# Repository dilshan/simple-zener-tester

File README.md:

# Experimental Zener Diode Tester

Automatic Zener diode tester is capable of identifying Zener diodes up to 27.5V. Apart from that, it can be used to recognize leads of the diodes/Zeners and detect damaged diodes.

This tester is designed using well-known ICs such as MC34063 and PIC16F88.

This unit provides approximately 5% to 15% accurate readings. Based on our observations, the accuracy of this unit can increase by using resistors with 1% tolerance, stable booster circuit, accurate sampling method(s), and with a more optimized PCB layout.

### More prototypes

The following photographs illustrate the prototype version build by [Boris Peshev](https://github.com/BaiBorko).

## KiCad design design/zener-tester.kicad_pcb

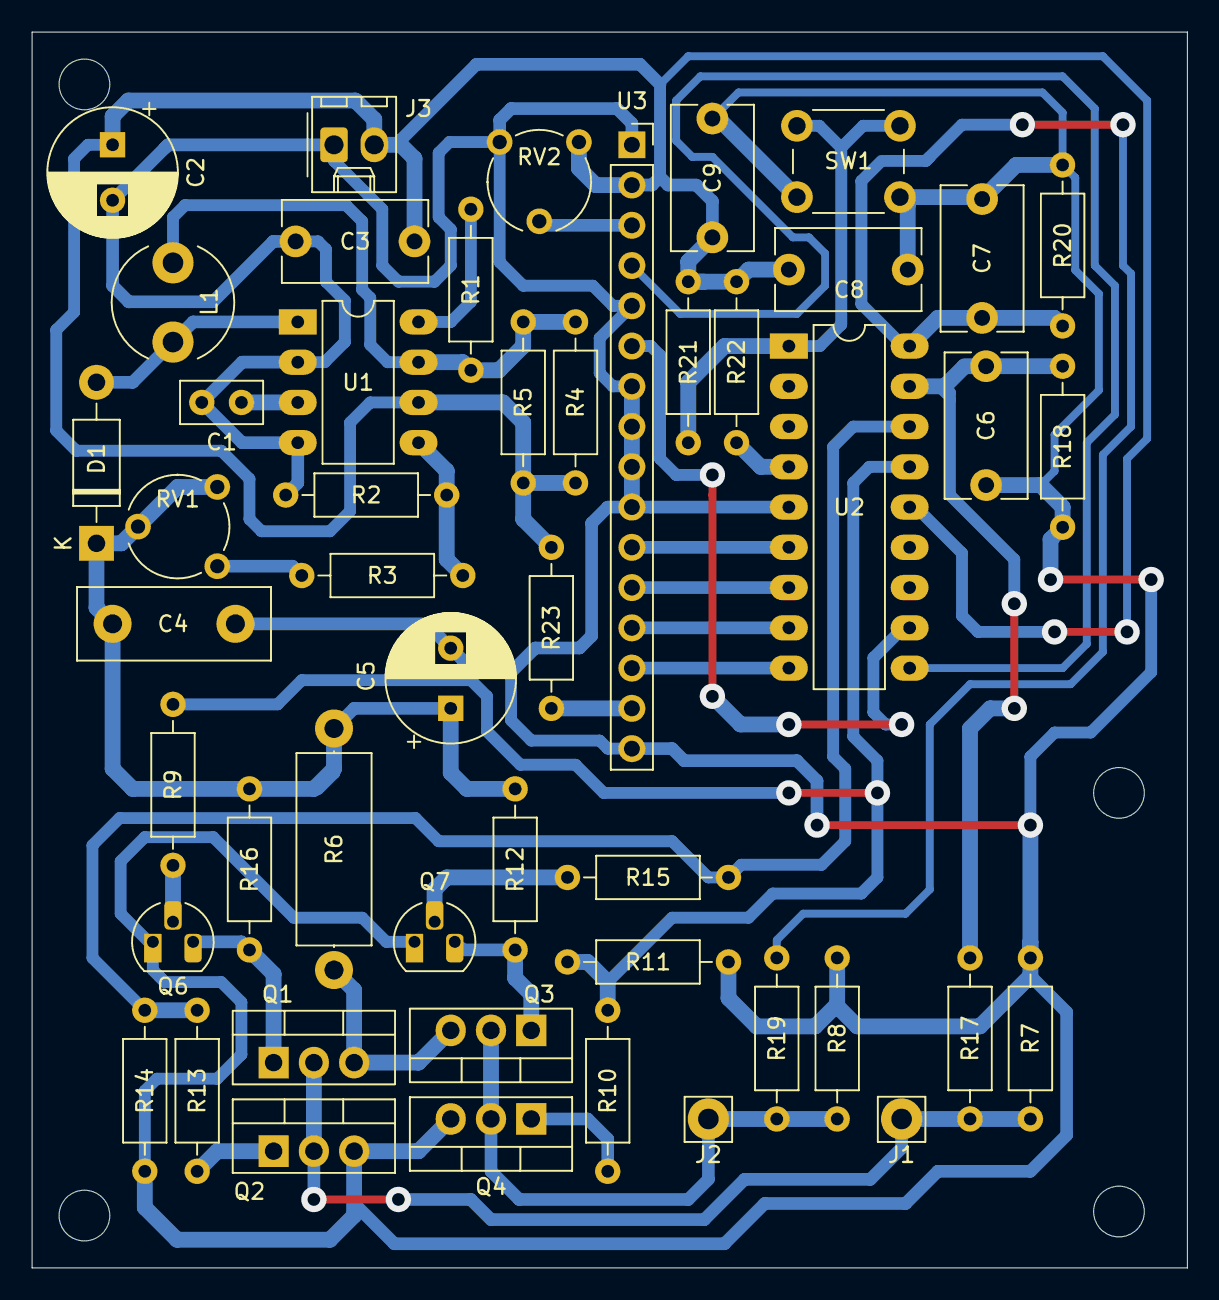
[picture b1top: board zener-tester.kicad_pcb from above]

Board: 2 copper layers, 72.9 x 78.0 mm, 53 parts (0 on the bottom side), 32 nets.

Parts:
 : MountingHole_3.2mm_M3
 #2,  #3,  #4: MountingHole_3.2mm_M3
C1: 0.001MFD; C_Disc_D5.0mm_W2.5mm_P2.50mm
C2: 100MFD; CP_Radial_D8.0mm_P3.50mm
C3, C6, C7, C8, C9: 0.1MFD; C_Disc_D9.0mm_W5.0mm_P7.50mm
C4: 0.033MFD; C_Disc_D12.0mm_W4.4mm_P7.75mm
C5: 220MFD; CP_Radial_D8.0mm_P3.80mm
D1: 1N5819; D_DO-41_SOD81_P10.16mm_Horizontal
J1: TEST-TERM-1; Pin_D1.3mm_L11.3mm_W2.8mm_Flat
J2: TEST-TERM-2; Pin_D1.3mm_L11.3mm_W2.8mm_Flat
J3: 5V-IN; Molex_KK-254_AE-6410-02A_1x02_P2.54mm_Vertical
L1: 220uH; L_Radial_D7.5mm_P5.00mm_Fastron_07P
Q1, Q3: IRF9540; TO-220-3_Vertical
Q2, Q4: IRF540; TO-220-3_Vertical
Q6, Q7: 2N4401; TO-92L_HandSolder
R1: 220R; R_Axial_DIN0207_L6.3mm_D2.5mm_P10.16mm_Horizontal
R2: 2.7K; R_Axial_DIN0207_L6.3mm_D2.5mm_P10.16mm_Horizontal
R3: 56K; R_Axial_DIN0207_L6.3mm_D2.5mm_P10.16mm_Horizontal
R4, R5: 1R; R_Axial_DIN0207_L6.3mm_D2.5mm_P10.16mm_Horizontal
R6: 1K; R_Axial_DIN0414_L11.9mm_D4.5mm_P15.24mm_Horizontal
R7, R8: 3.3M; R_Axial_DIN0207_L6.3mm_D2.5mm_P10.16mm_Horizontal
R9, R15, R21, R22: 22K; R_Axial_DIN0207_L6.3mm_D2.5mm_P10.16mm_Horizontal
R10, R13: 2.2K; R_Axial_DIN0207_L6.3mm_D2.5mm_P10.16mm_Horizontal
R11, R12, R14, R16: 10K; R_Axial_DIN0207_L6.3mm_D2.5mm_P10.16mm_Horizontal
R17, R19: 82K; R_Axial_DIN0207_L6.3mm_D2.5mm_P10.16mm_Horizontal
R18, R20: 15K; R_Axial_DIN0207_L6.3mm_D2.5mm_P10.16mm_Horizontal
R23: 470R; R_Axial_DIN0207_L6.3mm_D2.5mm_P10.16mm_Horizontal
RV1: 10K; Potentiometer_Piher_PT-6-V_Vertical
RV2: 20K; Potentiometer_Piher_PT-6-V_Vertical
SW1: TEST; SW_PUSH_6mm
U1: MC34063AP; DIP-8_W7.62mm_LongPads
U2: PIC16F88-IP; DIP-18_W7.62mm_LongPads
U3: RC1602A; PinSocket_1x16_P2.54mm_Vertical

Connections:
+5V: C2.1, C3.1, C8.1, C9.1, J3.2, R4.1, R5.1, R21.1, R22.1, R23.2, RV2.3, U1.6, U2.14, U3.2
GND: C1.2, C2.2, C3.2, C4.2, C5.2, C6.2, C7.2, C8.2, C9.2, J3.1, Q2.3, Q4.3, Q6.1, Q7.1, R2.1, R7.1, R8.2, R11.2, R14.2, R18.2, R20.2, RV2.1, SW1.2, U1.2, U1.4, U2.5, U3.1, U3.5, U3.7, U3.8, U3.9, U3.10, U3.16
LCD0: U2.6, U3.11
LCD1: U2.7, U3.12
LCD2: U2.8, U3.13
LCD3: U2.9, U3.14
LCD-EN: U2.11, U3.6
LCD-RS: U2.10, U3.4
LINE: C4.1, C5.1, D1.1, R6.2, R12.2, R16.2, RV1.1, RV1.2
MCLR: R22.2, U2.4
unnamed: C1.1, U1.3
unnamed: D1.2, L1.2, U1.1
unnamed: L1.1, R1.1, R4.2, R5.2, U1.7
unnamed: Q1.1, Q6.3, R16.1
unnamed: Q1.3, Q3.3, R6.1
unnamed: Q2.1, R13.2
unnamed: Q3.1, Q7.3, R12.1
unnamed: Q4.1, R10.1
unnamed: Q6.2, R9.2
unnamed: Q7.2, R15.1
unnamed: R1.2, U1.8
unnamed: R2.2, R3.1, U1.5
unnamed: R3.2, RV1.3
unnamed: R23.1, U3.15
unnamed: RV2.2, U3.3
SCAN-BTN: R21.2, SW1.1, U2.1
TEST-CH1: R9.1, R10.2, R11.1, U2.15
TEST-CH2: R13.1, R14.1, R15.2, U2.16
TP1: J1.1, Q1.2, Q2.2, R7.2, R17.1
TP2: J2.1, Q3.2, Q4.2, R8.1, R19.1
ZENER-SENCE1: C6.1, R17.2, R18.1, U2.17
ZENER-SENCE2: C7.1, R19.2, R20.1, U2.18

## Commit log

2020-05-23 Initial commit.
2020-05-23 Update readme with prototype image.
2021-06-10 Add feature to print on LCD the color of crocodile clips. R for red and B - for black in my case . Add pcb in sprint- layout format.
2021-06-11 Initial prototype of the Zener diode tester
2021-06-11 Add photographs of the Boris's build into the readme.md file.
2021-06-11 Fix formating issue in readme.md file.
2021-06-11 Fix error in readme.md file.
